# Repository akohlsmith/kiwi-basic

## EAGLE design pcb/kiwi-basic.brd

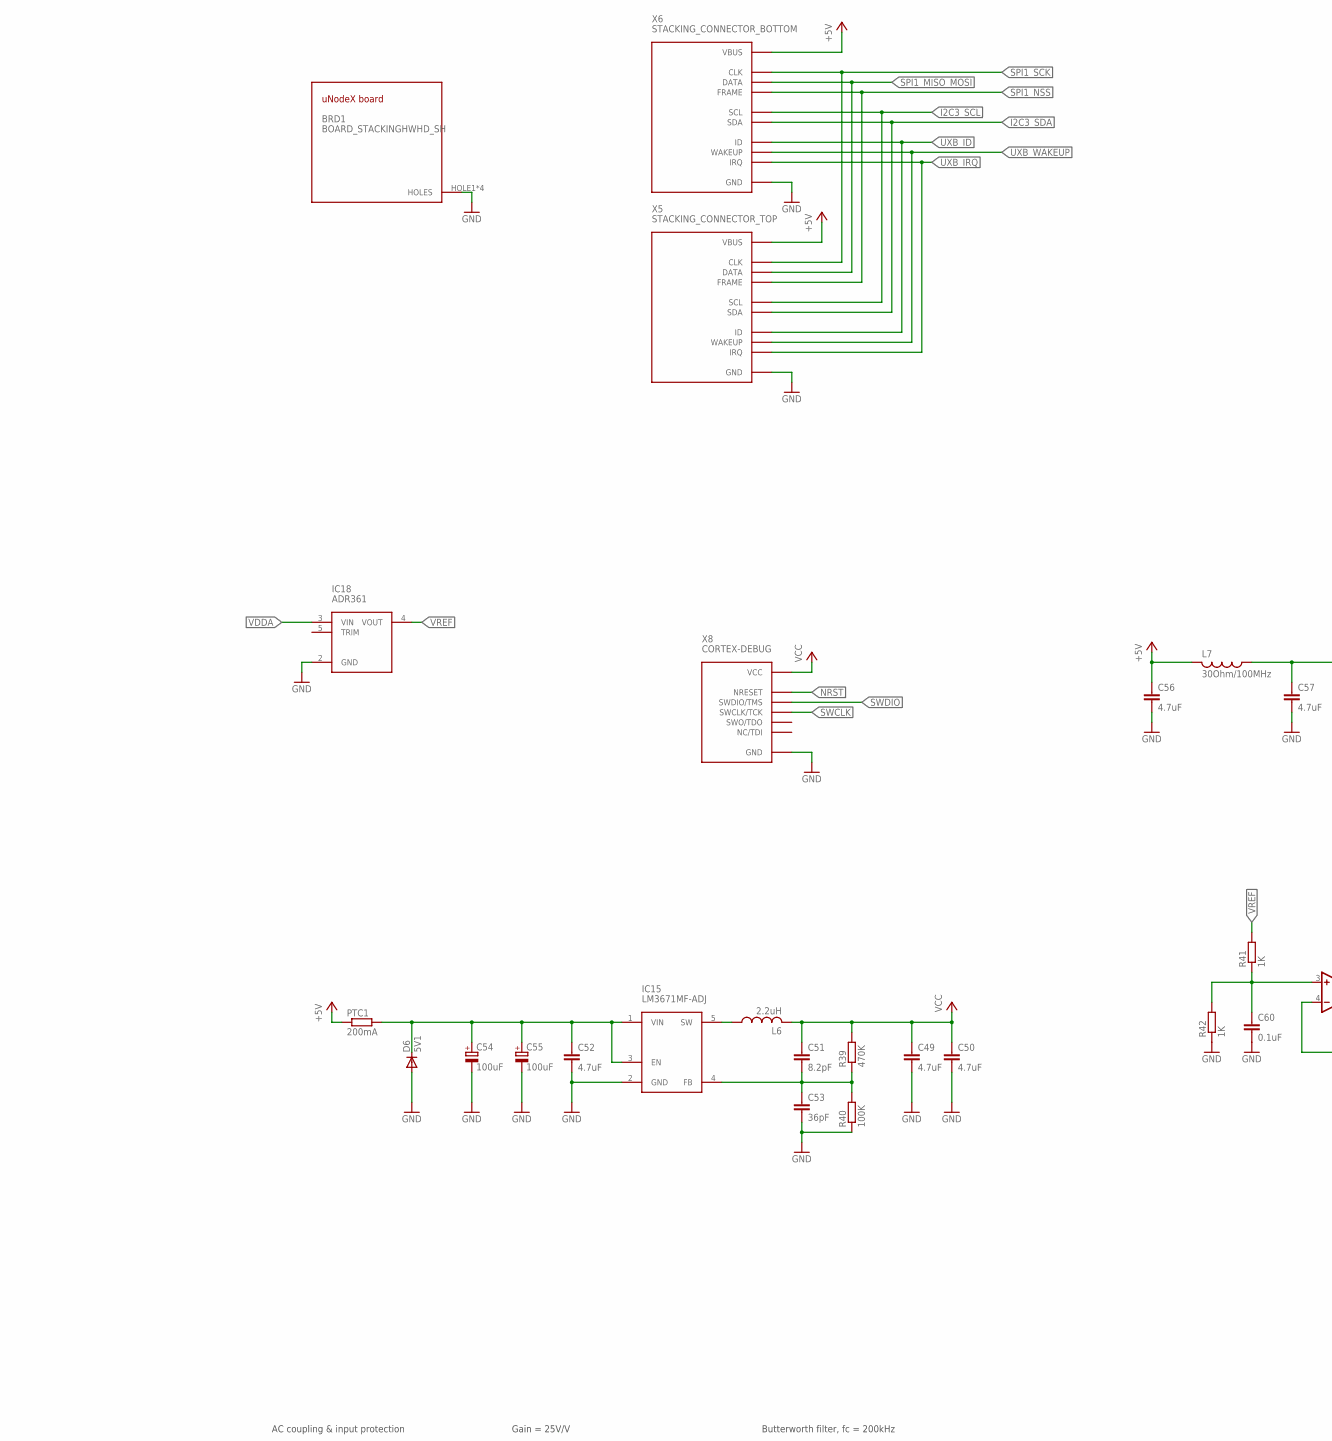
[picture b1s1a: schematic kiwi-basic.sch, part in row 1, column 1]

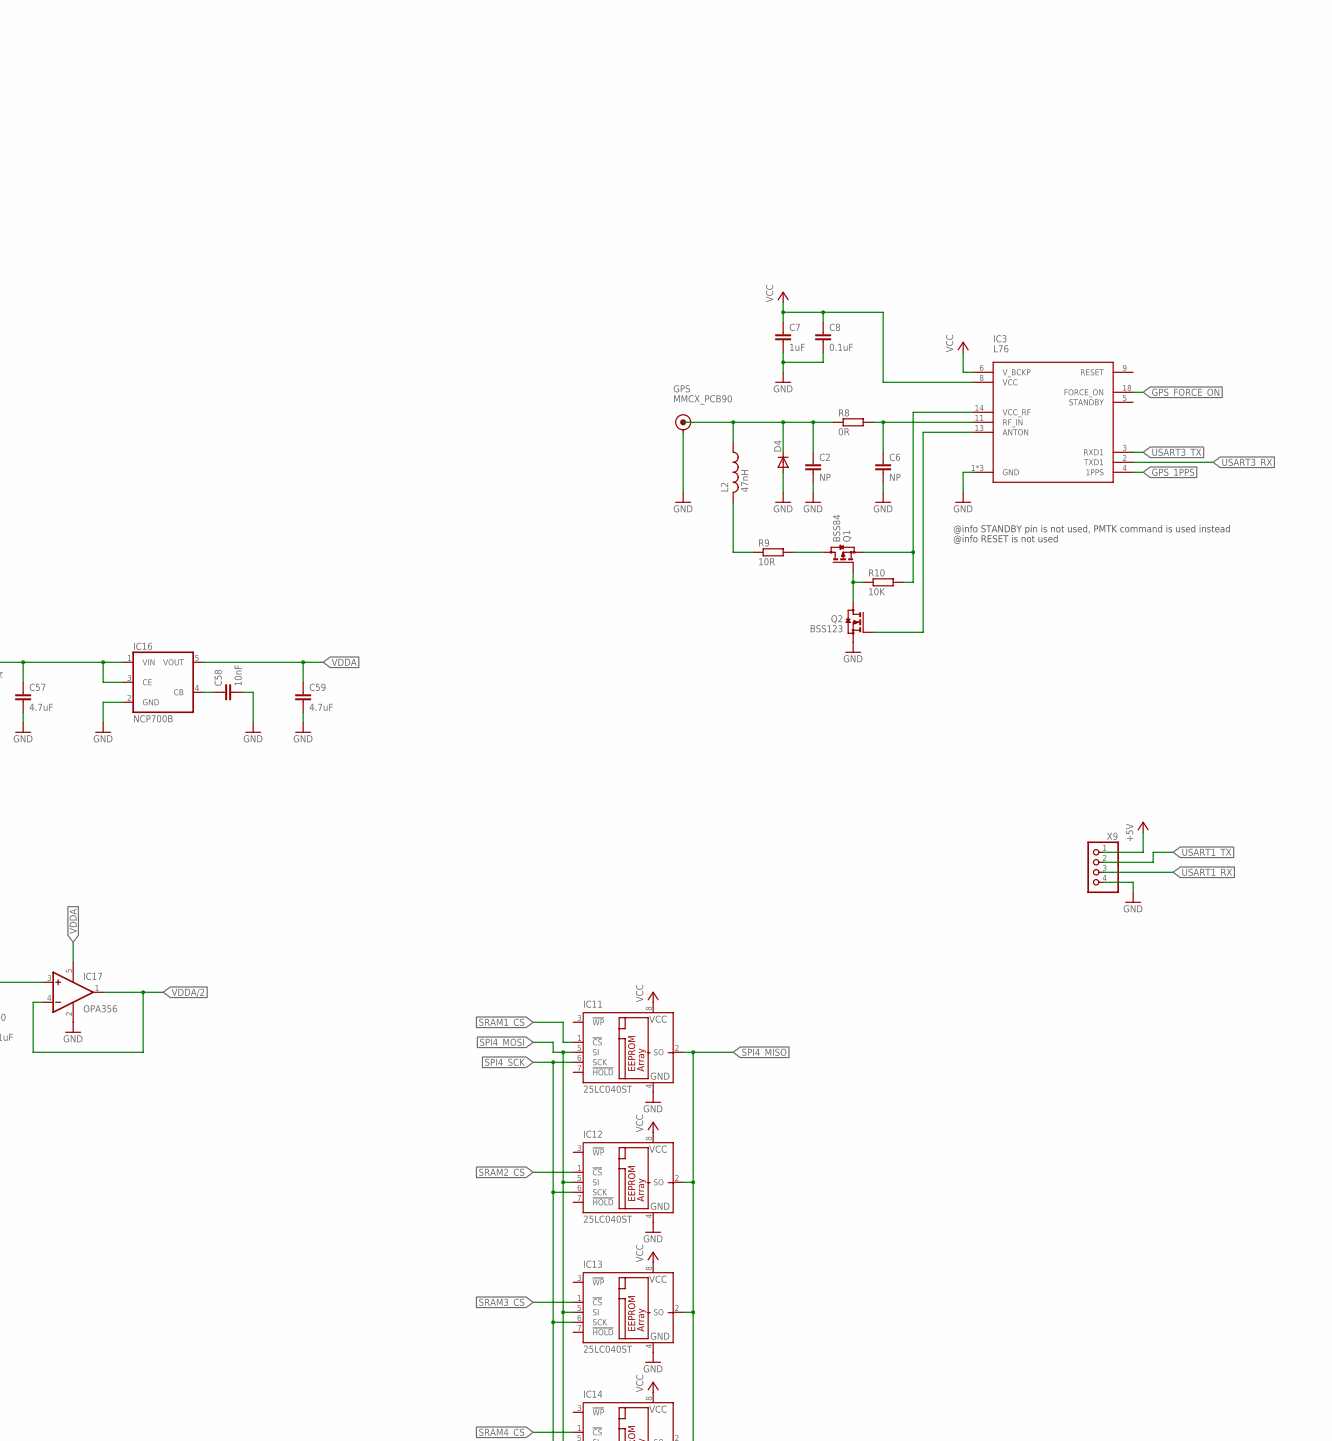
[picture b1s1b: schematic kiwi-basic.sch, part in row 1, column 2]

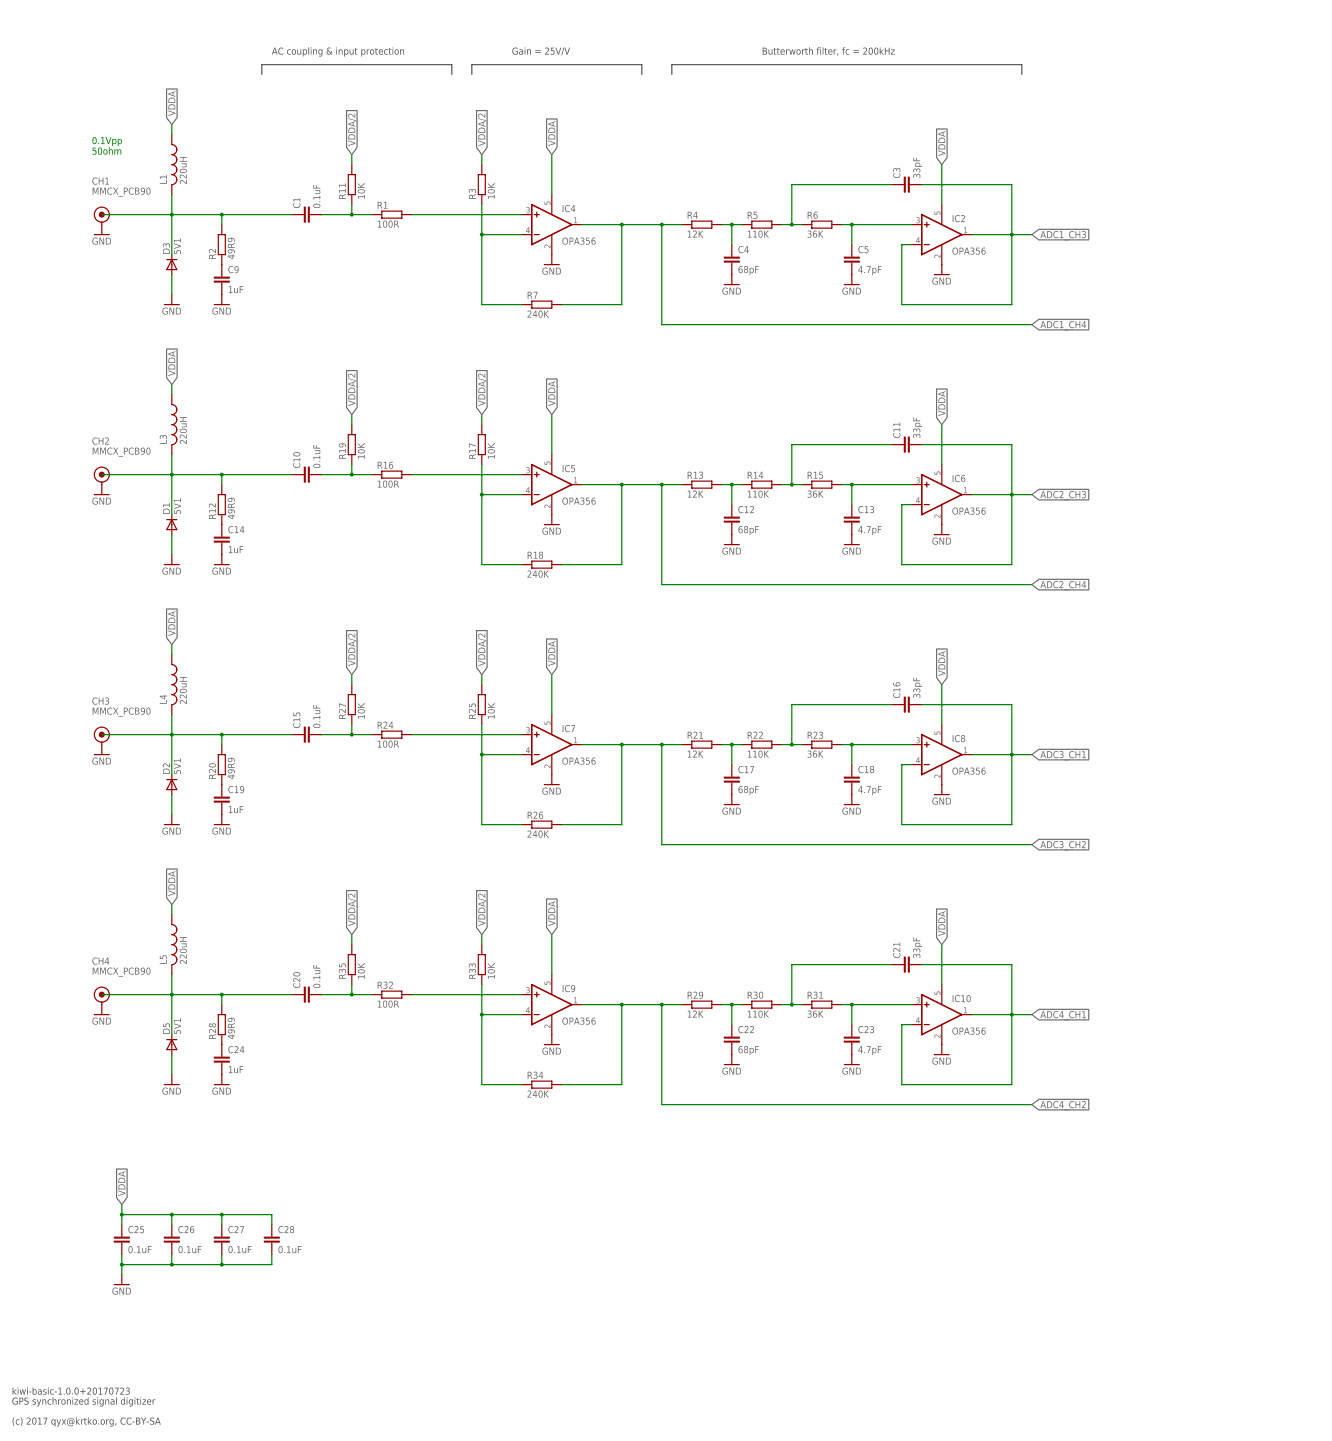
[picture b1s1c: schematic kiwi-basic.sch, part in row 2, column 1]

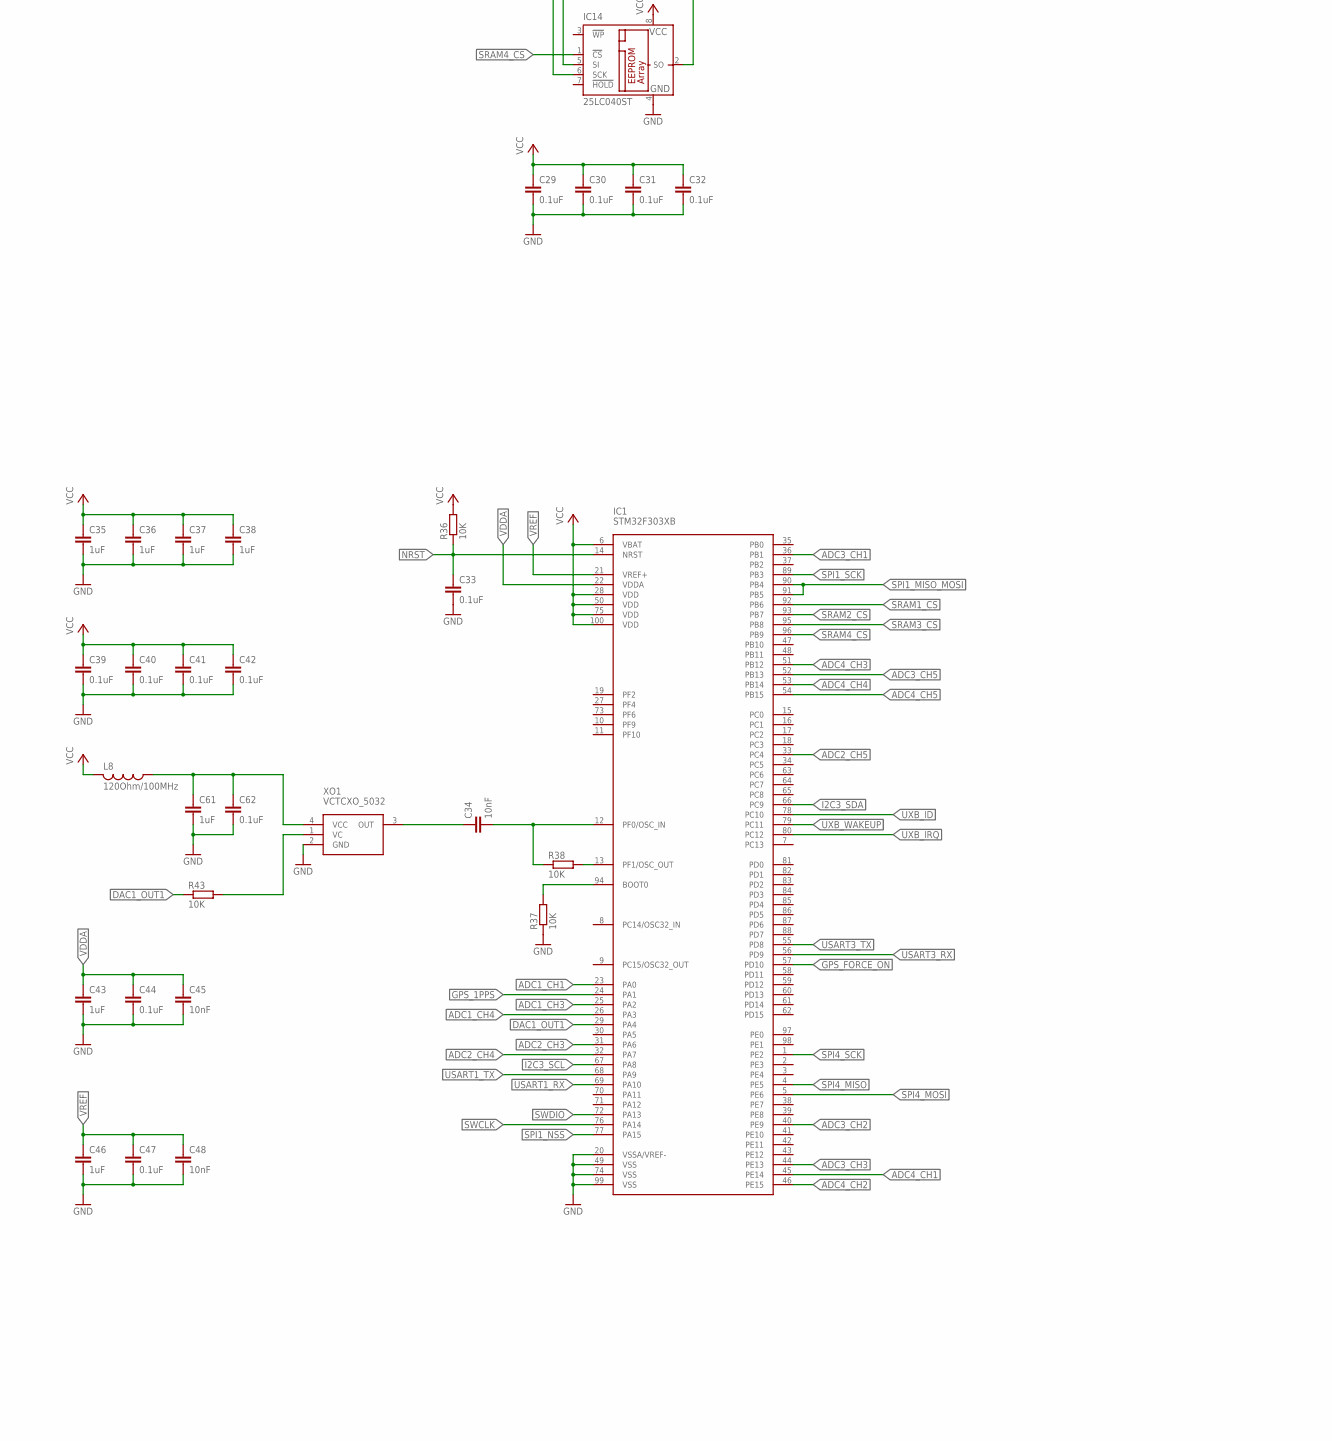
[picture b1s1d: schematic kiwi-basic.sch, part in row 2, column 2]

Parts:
BRD1: BOARD_STACKINGHWHD_SH; HWHD_SHARP_CORNERS
C1, C8, C10, C15, C20, C25, C26, C27, C28, C29, C30, C31, C32, C33, C39, C40, C41, C42, C44, C47, C60, C62: 0.1uF; C0603
C2, C6: NP; C0603
C3, C11, C16, C21: 33pF; C0603
C4, C12, C17, C22: 68pF; C0603
C5, C13, C18, C23: 4.7pF; C0603
C7, C9, C14, C19, C24, C35, C36, C37, C38, C43, C46, C61: 1uF; C0603
C34, C45, C48, C58: 10nF; C0603
C49, C50, C52, C56, C57, C59: 4.7uF; C0805
C51: 8.2pF; C0603
C53: 36pF; C0603
C54, C55: 100uF; PANASONIC_D
CH1, CH2, CH3, CH4: MMCX_PCB90; MMCX_PCB_90
D1, D2, D3, D5, D6: 5V1; SOD323-W
D4: DIODE-SOD323-W; SOD323-W
GPS: MMCX_PCB90; MMCX_PCB_90
IC1: STM32F303XB; TQFP100
IC2, IC4, IC5, IC6, IC7, IC8, IC9, IC10, IC17: OPA356; SOT23-5
IC3: L76
IC11, IC12, IC13, IC14: 25LC040ST; TSSOP8
IC15: LM3671MF-ADJ; SOT23-5
IC16: NCP700B; SOT25
IC18: ADR361; SOT23-5
L1, L3, L4, L5: 220uH; L2012C
L2: 47nH; L2012C
L6: 2.2uH; L2825P
L7: 30Ohm/100MHz; L2012C
L8: 120Ohm/100MHz; L2012C
PTC1: 200mA; R1206
Q1: BSS84; SOT23
Q2: BSS123; SOT23
R1, R16, R24, R32: 100R; R0603
R2, R12, R20, R28: 49R9; R0603
R3, R10, R11, R17, R19, R25, R27, R33, R35, R36, R37, R38, R43: 10K; R0603
R4, R13, R21, R29: 12K; R0603
R5, R14, R22, R30: 110K; R0603
R6, R15, R23, R31: 36K; R0603
R7, R18, R26, R34: 240K; R0603
R8: 0R; R0603
R9: 10R; R0603
R39: 470K; R0603
R40: 100K; R0603
R41, R42: 1K; R0603
X5: STACKING_CONNECTOR_TOP; HAR-FLEX-TOP-12P
X6: STACKING_CONNECTOR_BOTTOM; HAR-FLEX-BOTTOM-12P
X8: CORTEX-DEBUG
X9: PINHD-1X4; 1X04
XO1: VCTCXO_5032; XTAL_5032

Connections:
+5V: C56.1, L7.2, PTC1.1, X5.VBUS, X6.VBUS, X9.1
ADC1_CH1: IC1.23 (PA0)
ADC1_CH3: C3.2, IC1.25 (PA2), IC2.1 (OUT), IC2.4 (-IN)
ADC1_CH4: IC1.26 (PA3), IC4.1 (OUT), R4.1, R7.2
ADC2_CH3: C11.2, IC1.31 (PA6), IC6.1 (OUT), IC6.4 (-IN)
ADC2_CH4: IC1.32 (PA7), IC5.1 (OUT), R13.1, R18.2
ADC2_CH5: IC1.33 (PC4)
ADC3_CH1: C16.2, IC1.36 (PB1), IC8.1 (OUT), IC8.4 (-IN)
ADC3_CH2: IC1.40 (PE9), IC7.1 (OUT), R21.1, R26.2
ADC3_CH3: IC1.44 (PE13)
ADC3_CH5: IC1.52 (PB13)
ADC4_CH1: C21.2, IC1.45 (PE14), IC10.1 (OUT), IC10.4 (-IN)
ADC4_CH2: IC1.46 (PE15), IC9.1 (OUT), R29.1, R34.2
ADC4_CH3: IC1.51 (PB12)
ADC4_CH4: IC1.53 (PB14)
ADC4_CH5: IC1.54 (PB15)
DAC1_OUT1: IC1.29 (PA4), R43.1
GND: BRD1.HOLE1, BRD1.HOLE2, BRD1.HOLE3, BRD1.HOLE4, C2.2, C4.2, C5.2, C6.2, C7.2, C8.2, C9.2, C12.2, C13.2, C14.2, C17.2, C18.2, C19.2, C22.2, C23.2, C24.2, C25.2, C26.2, C27.2, C28.2, C29.2, C30.2, C31.2, C32.2, C33.2, C35.2, C36.2, C37.2, C38.2, C39.2, C40.2, C41.2, C42.2, C43.2, C44.2, C45.2, C46.2, C47.2, C48.2, C49.2, C50.2, C52.2, C53.2, C54.-, C55.-, C56.2, C57.2, C58.2, C59.2, C60.2, C61.2, C62.2, CH1.S1 (SHIELD), CH1.S2 (SHIELD), CH1.S3 (SHIELD), CH1.S4 (SHIELD), CH2.S1 (SHIELD), CH2.S2 (SHIELD), CH2.S3 (SHIELD), CH2.S4 (SHIELD), CH3.S1 (SHIELD), CH3.S2 (SHIELD), CH3.S3 (SHIELD), CH3.S4 (SHIELD), CH4.S1 (SHIELD), CH4.S2 (SHIELD), CH4.S3 (SHIELD), CH4.S4 (SHIELD), D1.A, D2.A, D3.A, D4.A, D5.A, D6.A, GPS.S1 (SHIELD), GPS.S2 (SHIELD), GPS.S3 (SHIELD), GPS.S4 (SHIELD), IC1.20 (VSSA/VREF-), IC1.49 (VSS), IC1.74 (VSS), IC1.99 (VSS), IC2.2 (V-), IC3.1 (GND), IC3.10 (GND), IC3.12 (GND), IC4.2 (V-), IC5.2 (V-), IC6.2 (V-), IC7.2 (V-), IC8.2 (V-), IC9.2 (V-), IC10.2 (V-), IC11.4 (GND), IC12.4 (GND), IC13.4 (GND), IC14.4 (GND), IC15.2 (GND), IC16.2 (GND), IC17.2 (V-), IC18.2 (GND), Q2.2 (S), R37.1, R40.1, R42.1, X5.GND1 (GND), X5.GND2 (GND), X5.GND3 (GND), X5.H1 (GND), X5.H2 (GND), X5.H3 (GND), X5.H4 (GND), X6.GND1 (GND), X6.GND2 (GND), X6.GND3 (GND), X6.H1 (GND), X6.H2 (GND), X6.H3 (GND), X6.H4 (GND), X8.GND1 (GND), X8.GND2 (GND), X8.GND_DETECT (GND), X9.4, XO1.2 (GND)
GPS_1PPS: IC1.24 (PA1), IC3.4 (1PPS)
GPS_FORCE_ON: IC1.57 (PD10), IC3.18 (FORCE_ON)
I2C3_SCL: IC1.67 (PA8), X5.SCL, X6.SCL
I2C3_SDA: IC1.66 (PC9), X5.SDA, X6.SDA
unnamed: C9.1, R2.1
unnamed: IC4.3 (+IN), R1.2
unnamed: C1.1, CH1.C (CENTER), D3.C, L1.2, R2.2
unnamed: C1.2, R1.1, R11.1
unnamed: C4.1, R4.2, R5.1
unnamed: C3.1, R5.2, R6.1
unnamed: C5.1, IC2.3 (+IN), R6.2
unnamed: IC4.4 (-IN), R3.1, R7.1
unnamed: C10.1, CH2.C (CENTER), D1.C, L3.2, R12.2
unnamed: C2.1, D4.C, GPS.C (CENTER), L2.1, R8.1
unnamed: C6.1, IC3.11 (RF_IN), R8.2
unnamed: L2.2, R9.1
unnamed: IC3.14 (VCC_RF), Q1.2 (S), R10.2
unnamed: Q1.3 (D), R9.2
unnamed: Q1.1 (G), Q2.3 (D), R10.1
unnamed: IC3.13 (ANTON), Q2.1 (G)
unnamed: C12.1, R13.2, R14.1
unnamed: C11.1, R14.2, R15.1
unnamed: C13.1, IC6.3 (+IN), R15.2
unnamed: IC5.4 (-IN), R17.1, R18.1
unnamed: IC5.3 (+IN), R16.2
unnamed: C14.1, R12.1
unnamed: C10.2, R16.1, R19.1
unnamed: C15.1, CH3.C (CENTER), D2.C, L4.2, R20.2
unnamed: C17.1, R21.2, R22.1
unnamed: C16.1, R22.2, R23.1
unnamed: C18.1, IC8.3 (+IN), R23.2
unnamed: IC7.4 (-IN), R25.1, R26.1
unnamed: IC7.3 (+IN), R24.2
unnamed: C19.1, R20.1
unnamed: C15.2, R24.1, R27.1
unnamed: C20.1, CH4.C (CENTER), D5.C, L5.2, R28.2
unnamed: C22.1, R29.2, R30.1
unnamed: C21.1, R30.2, R31.1
unnamed: C23.1, IC10.3 (+IN), R31.2
unnamed: IC9.4 (-IN), R33.1, R34.1
unnamed: IC9.3 (+IN), R32.2
unnamed: C24.1, R28.1
unnamed: C20.2, R32.1, R35.1
unnamed: IC1.94 (BOOT0), R37.2
unnamed: IC1.13 (PF1/OSC_OUT), R38.2
unnamed: C51.2, C53.1, IC15.4 (FB), R39.1, R40.2
unnamed: IC15.5 (SW), L6.1
unnamed: C57.1, IC16.1 (VIN), IC16.3 (CE), L7.1
unnamed: C58.1, IC16.4 (CB)
unnamed: C60.1, IC17.3 (+IN), R41.1, R42.2
unnamed: C34.1, XO1.3 (OUT)
unnamed: C61.1, C62.1, L8.1, XO1.4 (VCC)
unnamed: R43.2, XO1.1 (VC)
NRST: C33.1, IC1.14 (NRST), R36.1, X8.NRESET
SPI1_MISO_MOSI: IC1.90 (PB4), IC1.91 (PB5), X5.DATA, X6.DATA
SPI1_NSS: IC1.77 (PA15), X5.FRAME, X6.FRAME
SPI1_SCK: IC1.89 (PB3), X5.CLK, X6.CLK
SPI4_MISO: IC1.4 (PE5), IC11.2 (SO), IC12.2 (SO), IC13.2 (SO), IC14.2 (SO)
SPI4_MOSI: IC1.5 (PE6), IC11.5 (SI), IC12.5 (SI), IC13.5 (SI), IC14.5 (SI)
SPI4_SCK: IC1.1 (PE2), IC11.6 (SCK), IC12.6 (SCK), IC13.6 (SCK), IC14.6 (SCK)
SRAM1_CS: IC1.92 (PB6), IC11.1 (!CS)
SRAM2_CS: IC1.93 (PB7), IC12.1 (!CS)
SRAM3_CS: IC1.95 (PB8), IC13.1 (!CS)
SRAM4_CS: IC1.96 (PB9), IC14.1 (!CS)
SWCLK: IC1.76 (PA14), X8.SWCLK/TCK
SWDIO: IC1.72 (PA13), X8.SWDIO/TMS
TCXO_CLK: C34.2, IC1.12 (PF0/OSC_IN), R38.1
USART1_RX: IC1.69 (PA10), X9.3
USART1_TX: IC1.68 (PA9), X9.2
USART3_RX: IC1.56 (PD9), IC3.2 (TXD1)
USART3_TX: IC1.55 (PD8), IC3.3 (RXD1)
UXB_ID: IC1.78 (PC10), X5.ID, X6.ID
UXB_IRQ: IC1.80 (PC12), X5.IRQ, X6.IRQ
UXB_WAKEUP: IC1.79 (PC11), X5.WAKEUP, X6.WAKEUP
VBUS: C52.1, C54.+, C55.+, D6.C, IC15.1 (VIN), IC15.3 (EN), PTC1.2
VCC: C7.1, C8.1, C29.1, C30.1, C31.1, C32.1, C35.1, C36.1, C37.1, C38.1, C39.1, C40.1, C41.1, C42.1, C49.1, C50.1, C51.1, IC1.6 (VBAT), IC1.28 (VDD), IC1.50 (VDD), IC1.75 (VDD), IC1.100 (VDD), IC3.6 (V_BCKP), IC3.8 (VCC), IC11.8 (VCC), IC12.8 (VCC), IC13.8 (VCC), IC14.8 (VCC), L6.2, L8.2, R36.2, R39.2, X8.VCC
VDDA: C25.1, C26.1, C27.1, C28.1, C43.1, C44.1, C45.1, C59.1, IC1.22 (VDDA), IC2.5 (V+), IC4.5 (V+), IC5.5 (V+), IC6.5 (V+), IC7.5 (V+), IC8.5 (V+), IC9.5 (V+), IC10.5 (V+), IC16.5 (VOUT), IC17.5 (V+), IC18.3 (VIN), L1.1, L3.1, L4.1, L5.1
VDDA/2: IC17.1 (OUT), IC17.4 (-IN), R3.2, R11.2, R17.2, R19.2, R25.2, R27.2, R33.2, R35.2
VREF: C46.1, C47.1, C48.1, IC1.21 (VREF+), IC18.4 (VOUT), R41.2

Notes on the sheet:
Gain = 25V/V
Butterworth filter, fc = 200kHz
AC coupling & input protection
@info STANDBY pin is not used, PMTK command is used instead
@info RESET is not used
0.1Vpp 50ohm
(c) 2017 qyx@krtko.org, CC-BY-SA
kiwi-basic-1.0.0+20170723
GPS synchronized signal digitizer

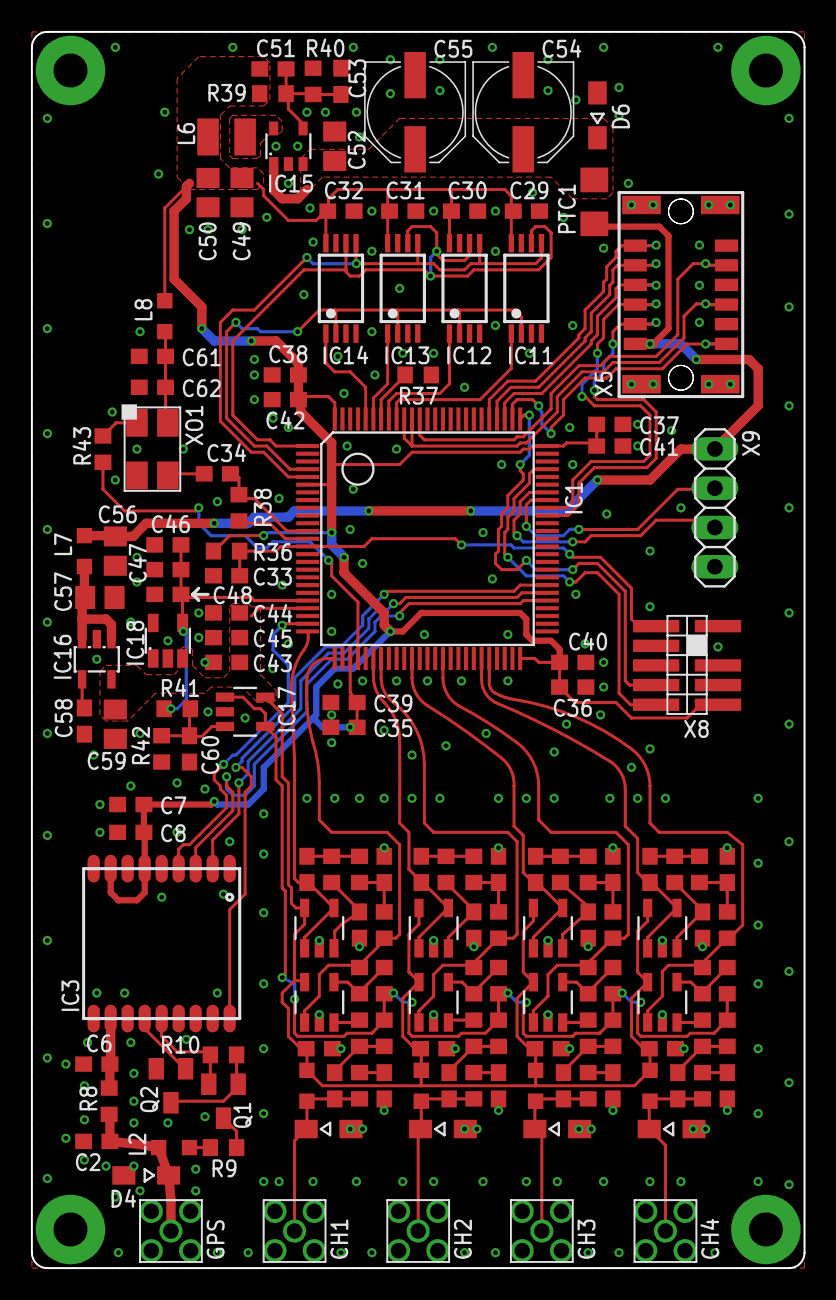
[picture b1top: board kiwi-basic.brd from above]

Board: 2 copper layers, 50.0 x 80.0 mm, 151 parts (0 on the bottom side), 90 nets.

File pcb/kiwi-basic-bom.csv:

"Qty";"Value";"Device";"Package";"Parts";"Description";"MF";"MPN";"OC_FARNELL";"OC_NEWARK";
"1";"";"DIODE-SOD323-W";"SOD323-W";"D4";"DIODE";"";"";"";"";
"1";"";"PINHD-1X4";"1X04";"JP1";"PIN HEADER";"";"";"";"";
"22";"0.1uF";"C-EUC0603";"C0603";"C1, C8, C10, C15, C20, C25, C26, C27, C28, C29, C30, C31, C32, C33, C39, C40, C41, C42, C44, C47, C60, C62";"CAPACITOR, European symbol";"";"";"";"";
"1";"0R";"R-EU_R0603";"R0603";"R8";"RESISTOR, European symbol";"";"";"";"";
"1";"100K";"R-EU_R0603";"R0603";"R40";"RESISTOR, European symbol";"";"";"";"";
"4";"100R";"R-EU_R0603";"R0603";"R1, R16, R24, R32";"RESISTOR, European symbol";"";"";"";"";
"2";"100uF";"CPOL-EUD";"PANASONIC_D";"C54, C55";"POLARIZED CAPACITOR, European symbol";"";"";"";"";
"9";"10K";"R-EU_R0603";"R0603";"R10, R11, R19, R27, R35, R36, R37, R38, R43";"RESISTOR, European symbol";"";"";"";"";
"1";"10R";"R-EU_R0603";"R0603";"R9";"RESISTOR, European symbol";"";"";"";"";
"4";"10nF";"C-EUC0603";"C0603";"C34, C45, C48, C58";"CAPACITOR, European symbol";"";"";"";"";
"4";"110K";"R-EU_R0603";"R0603";"R5, R14, R22, R30";"RESISTOR, European symbol";"";"";"";"";
"1";"120Ohm/100MHz";"L-USL2012C";"L2012C";"L8";"INDUCTOR, American symbol";"";"";"";"";
"4";"12K";"R-EU_R0603";"R0603";"R4, R13, R21, R29";"RESISTOR, European symbol";"";"";"";"";
"6";"1K";"R-EU_R0603";"R0603";"R3, R17, R25, R33, R41, R42";"RESISTOR, European symbol";"";"";"";"";
"12";"1uF";"C-EUC0603";"C0603";"C7, C9, C14, C19, C24, C35, C36, C37, C38, C43, C46, C61";"CAPACITOR, European symbol";"";"";"";"";
"1";"2.2uH";"L-USL2825P";"L2825P";"L6";"INDUCTOR, American symbol";"";"";"";"";
"1";"200mA";"R-EU_R1206";"R1206";"PTC1";"RESISTOR, European symbol";"";"";"";"";
"4";"220uH";"L-USL2012C";"L2012C";"L1, L3, L4, L5";"INDUCTOR, American symbol";"";"";"";"";
"4";"24K";"R-EU_R0603";"R0603";"R7, R18, R26, R34";"RESISTOR, European symbol";"";"";"";"";
"4";"25LC040ST";"25LC040ST";"TSSOP8";"IC11, IC12, IC13, IC14";"Serial EEPROM 4K/ 8K , SPI bus";"MICROCHIP";"25LC040A-I/ST";"1815998";"72J3684";
"1";"30Ohm/100MHz";"L-USL2012C";"L2012C";"L7";"INDUCTOR, American symbol";"";"";"";"";
"4";"33pF";"C-EUC0603";"C0603";"C3, C11, C16, C21";"CAPACITOR, European symbol";"";"";"";"";
"4";"36K";"R-EU_R0603";"R0603";"R6, R15, R23, R31";"RESISTOR, European symbol";"";"";"";"";
"1";"36pF";"C-EUC0603";"C0603";"C53";"CAPACITOR, European symbol";"";"";"";"";
"4";"4.7pF";"C-EUC0603";"C0603";"C5, C13, C18, C23";"CAPACITOR, European symbol";"";"";"";"";
"6";"4.7uF";"C-EUC0805";"C0805";"C49, C50, C52, C56, C57, C59";"CAPACITOR, European symbol";"";"";"";"";
"1";"470K";"R-EU_R0603";"R0603";"R39";"RESISTOR, European symbol";"";"";"";"";
"1";"47nH";"L-USL2012C";"L2012C";"L2";"INDUCTOR, American symbol";"";"";"";"";
"4";"49R9";"R-EU_R0603";"R0603";"R2, R12, R20, R28";"RESISTOR, European symbol";"";"";"";"";
"5";"5V1";"DIODE-SOD323-W";"SOD323-W";"D1, D2, D3, D5, D6";"DIODE";"";"";"";"";
"4";"68pF";"C-EUC0603";"C0603";"C4, C12, C17, C22";"CAPACITOR, European symbol";"";"";"";"";
"1";"8.2pF";"C-EUC0603";"C0603";"C51";"CAPACITOR, European symbol";"";"";"";"";
"1";"ADR361";"ADR361";"SOT23-5";"IC18";"";"";"";"";"";
"1";"BOARD_STACKINGHWHD_SH";"BOARD_STACKINGHWHD_SH";"HWHD_SHARP_CORNERS";"BRD1";"";"";"";"";"";
"1";"BSS123";"BSS123";"SOT23";"Q2";"N-CHANNEL MOS FET";"";"";"";"";
"1";"BSS84";"BSS84";"SOT23";"Q1";"P-CHANNEL MOS FET";"";"";"";"";
"1";"CORTEX-DEBUG";"CORTEX-DEBUG";"CORTEX-DEBUG";"X8";"";"";"";"";"";
"1";"L76";"L76";"L76";"IC3";"";"";"";"";"";
"1";"LM3671MF-ADJ";"LM3671MF";"SOT23-5";"IC15";"";"";"";"";"";
"5";"MMCX_PCB90";"MMCX_PCB90";"MMCX_PCB_90";"X1, X2, X3, X4, X7";"";"";"";"";"";
"1";"NCP700B";"TS520530";"SOT25";"IC16";"150mA Low Noise LDO Voltage Regulator with Enable";"";"";"";"";
"2";"NP";"C-EUC0603";"C0603";"C2, C6";"CAPACITOR, European symbol";"";"";"";"";
"9";"OPA356";"MCP601OT";"SOT23-5";"IC2, IC4, IC5, IC6, IC7, IC8, IC9, IC10, IC17";"Single Op Amp 2.7V to 6.0V Single Supply CMOS";"";"";"";"";
"1";"STACKING_CONNECTOR_BOTTOM";"STACKING_CONNECTOR_BOTTOM";"HAR-FLEX-BOTTOM-12P";"X6";"";"";"";"";"";
"1";"STACKING_CONNECTOR_TOP";"STACKING_CONNECTOR_TOP";"HAR-FLEX-TOP-12P";"X5";"";"";"";"";"";
"1";"STM32F303XB";"STM32F303XB";"TQFP100";"IC1";"";"";"";"";"";
"1";"VCTCXO_5032";"VCTCXO_5032";"XTAL_5032";"XO1";"";"";"";"";"";

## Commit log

2017-09-06 Initial commit, add libopencm3 submodule
2017-09-06 Add a proof of concept code
2017-09-06 Add schematic and layout of the PCB
2017-09-06 Add .gitignore to ignore Eagle backup files, lock files and compiled code
2017-09-06 Move the GPSDO stuff to a separate file
2017-10-31 Add Gerber outputs (seeedstudio names)
2018-02-08 Add UXB support and refactor GPSDO code
2018-02-08 Move sampler code to a dedicated file
2018-02-13 UXB bus communication support
    Portions of the code were refactored. Sampler code was commeted
    more verbosely.
    Basic UXB implementation was done (libuxb, uxb_slave added) together
    with a waveform source definition (.proto).It is meant to be used
    for testing only.
